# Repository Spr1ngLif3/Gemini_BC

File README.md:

<!-- PROJECT LOGO -->
<br />
<div align="center">

  <h3 align="center">Gemini Board Computer</h3>

  <p align="center">
    A simple and affordable board computer for bistage rockets!
    <br />
    <br />
    <a href="https://github.com/Spr1ngLif3/Gemini_BC/tree/master/software">Scripts</a>
    &middot;
    <a href="https://github.com/Spr1ngLif3/Gemini_BC/tree/master/hardware/gerbers">Gerbers</a>
    &middot;
    <a href="https://github.com/Spr1ngLif3/Gemini_BC/issues/new/choose">Request Feature</a>
  </p>
</div>

<!-- TABLE OF CONTENTS -->
<details>
  <summary>Table of Contents</summary>
  <ol>
    <li>
      <a href="#about-the-project">About The Project</a>
    </li>
    <li>
      <a href="#getting-started">Getting Started</a>
      <ul>
        <li><a href="#hardware">Hardware</a></li>
        <li><a href="#software">Software</a></li>
      </ul>
    </li>
    <li><a href="#usage">Usage</a></li>
    <li><a href="#contributing">Contributing</a></li>
    <li><a href="#license">License</a></li>
    <li><a href="#contact">Contact</a></li>
    <li><a href="#acknowledgments">Acknowledgments</a></li>
  </ol>
</details>

<!-- ABOUT THE PROJECT -->
## About The Project
<div align="center">

</div>

<br>

Building avionics for rockets can be really difficult: you have to choose the microcontroller, the sensors and how to use it for implement all the feature you want.

The experience looks overwhelming.

This is the right project for you! I developed a first simple platform to implement a complete bistage rocket avionic. This board contains the essential parts for satisfy only two tasks:

1. Starting the second stage of a rocket.
2. Log all the data from the launch in a microSD card.

I used a cheap and modular microcontroller (the Raspberry Pi Pico) for control all the components and I programmed it with the easiest programming language in the world: Python.

<p align="right">(<a href="#readme-top">back to top</a>)</p>

<!-- GETTING STARTED -->
## Getting Started

### Hardware

The board is designed with [KiCAD](https://kicad.org) software, an open source for making schematics and PCBs. 

For editing and take a look to the project, you can open KiCAD and select the option **Open Project (CTRL + O)** in the top-left menu.

After that, **select the .kicd_pro file** in the `hardware` folder.

If you want to send in production the board (with serivces like JLCPCB or PCBWay etc.) you can **zip the `gerbers` folder** and upload the zip file to the production service site. I can also modify the PCB and regenerate the gerbers via KiCAD and make your own board.

#### Note!!!
The KiCAD project needs the TP4056 battery manager footprint to work. You can find it in the `utils` folder. For help KiCAD recognize it, **move the .kicad_mod file in the same folder of the project file**. If you notice some problems, please open a issue or [contact me](#contact).

### Software

1. Install VSCode and setup the environment for the Raspberry Pi Pico. Check this [tutorial](https://randomnerdtutorials.com/raspberry-pi-pico-vs-code-micropython/) (not related to me).
2. Clone the repo.
   ```sh
   git clone https://github.com/Spr1ngLif3/Gemini_BC.git
   ```
3. Open the `software` folder in VSCode.
   ```sh
   code Gemini_BC/software
   ```
4. Now you can upload the basic script on the board with the command **MicroPico: Upload current file to Pico**. 

**Please do your checks before uploading the scripts and put the board inside a rocket! I'm not responsible for all missusage of this scripts.**

5. Board ready for launch.

<p align="right">(<a href="#readme-top">back to top</a>)</p>

<!-- USAGE EXAMPLES -->
## Usage

For using it in the wild (in the rocket), be careful to the polarity of the connectors on the board. The battery has a specific polarity but not the igniter (it should not care). I tested the board with some solid rocket engines designed for small rocket models, and I adjusted the timer for the second stage ignition based on the simulation and the specs of the engine.

The board can also charge the battery itself via USB-C with the TP4056 module on board.

Before the launch, be sure that the microSD card is correctly inserted and formatted in the FAT32 filesystem, the battery led is solid blue and the board is well secured on the rocket body.

After that, when you pull the switch to on the Pico boot and start executing the script loaded in it.

<p align="right">(<a href="#readme-top">back to top</a>)</p>

<!-- CONTRIBUTING -->
## Contributing

Contributions are what make the open source community such an amazing place to learn, inspire, and create. Any contributions you make are **greatly appreciated**.

If you have a suggestion that would make this better, please fork the repo and create a pull request. You can also simply open an issue.
Don't forget to give the project a star! Thanks again!

1. Fork the Project
2. Create your Feature Branch (`git checkout -b feature/AmazingFeature`)
3. Commit your Changes (`git commit -m 'Add some AmazingFeature'`)
4. Push to the Branch (`git push origin feature/AmazingFeature`)
5. Open a Pull Request

<p align="right">(<a href="#readme-top">back to top</a>)</p>

<!-- LICENSE -->
## License
Hardware files are licensed under CERN-OHL-S v2.

Software and scripts are licensed under GPLv3.

See `LICENSE` folder for more information.

<p align="right">(<a href="#readme-top">back to top</a>)</p>

<!-- CONTACT -->
## Contact

IG: [@ilvecchiourlatore](https://instagram.com/ilvecchiourlatore)

Website: [SpaceZero](https://spacezero.it)

<p align="right">(<a href="#readme-top">back to top</a>)</p>

<!-- ACKNOWLEDGMENTS -->
## Acknowledgments

I list here some resources that I feel useful for you:

* [MicroPython Docs](https://docs.micropython.org/en/latest/)
* [Raspberry Pi Pico Docs](https://www.raspberrypi.com/documentation/microcontrollers/pico-series.html)
* [KiCAD Docs](https://docs.kicad.org/)

<p align="right">(<a href="#readme-top">back to top</a>)</p>

Made with <3 by an hacker.

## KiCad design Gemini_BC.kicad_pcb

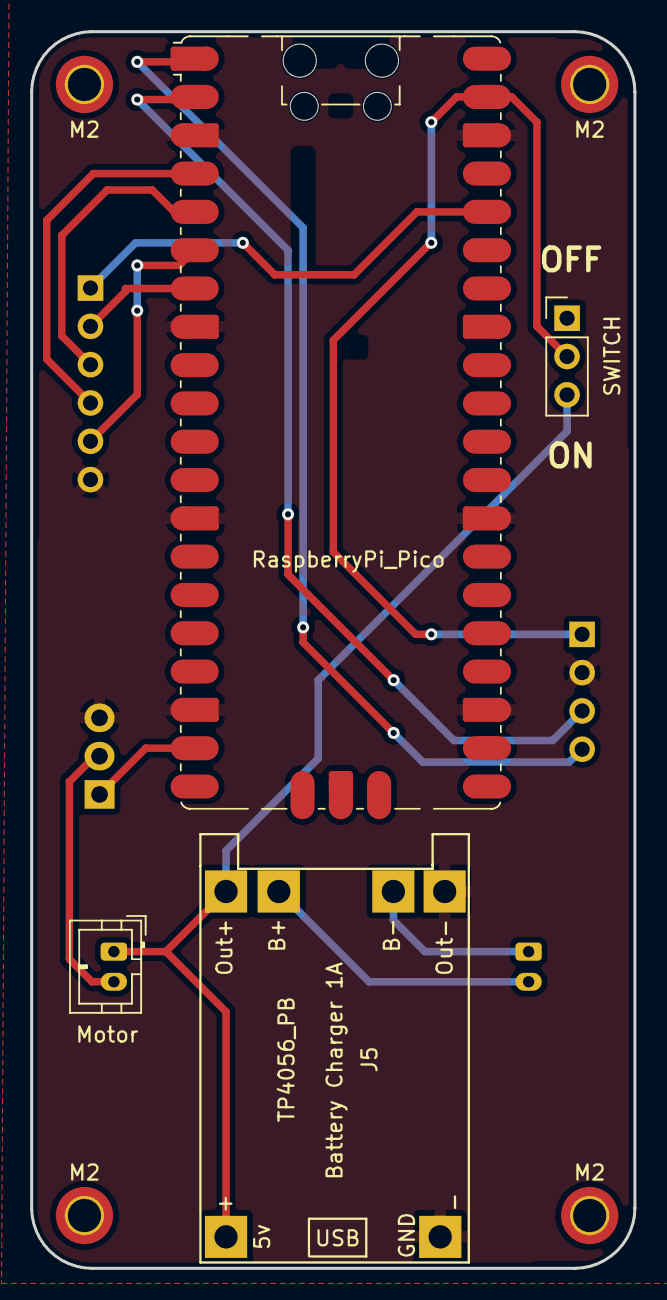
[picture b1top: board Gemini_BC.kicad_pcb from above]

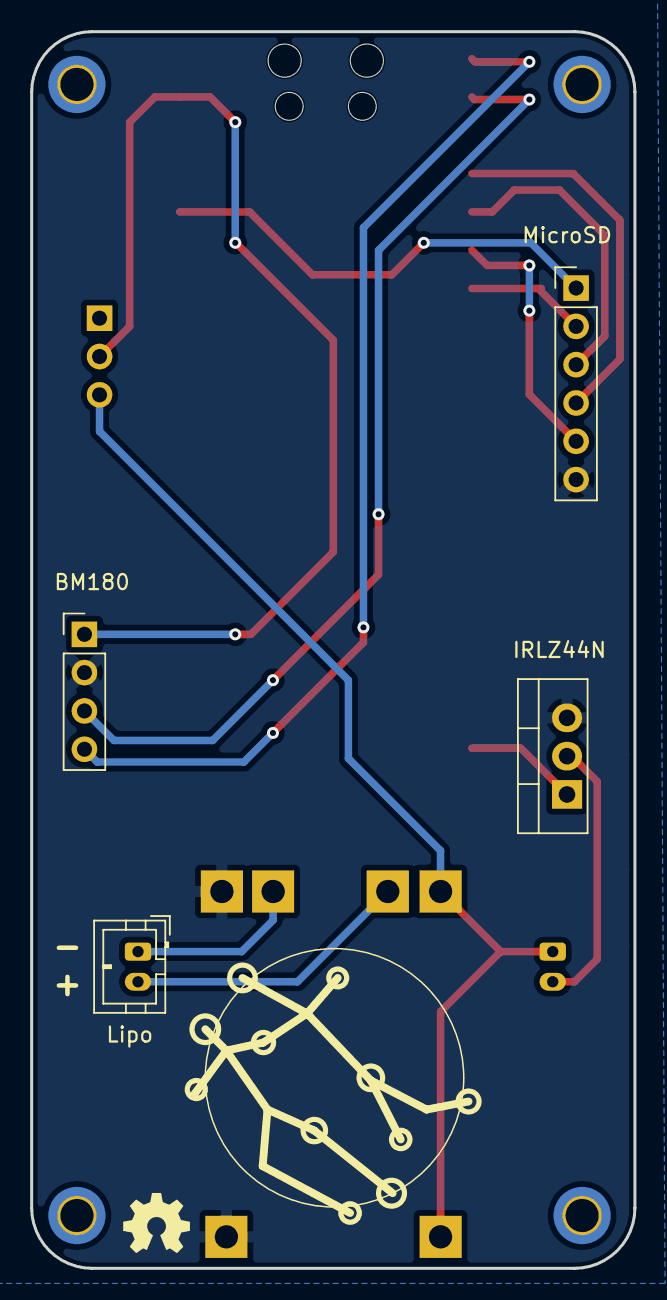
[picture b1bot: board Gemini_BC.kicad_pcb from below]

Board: 2 copper layers, 40.0 x 82.0 mm, 12 parts (4 on the bottom side), 14 nets.

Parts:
A1: RaspberryPi_Pico; RaspberryPi_Pico_SMD_HandSolder
J1: BM180; PinHeader_1x04_P2.54mm_Vertical
J2: MicroSD; PinHeader_1x06_P2.54mm_Vertical
J3: Lipo; JST_PH_B2B-PH-K_1x02_P2.00mm_Vertical
J4: Motor; JST_PH_B2B-PH-K_1x02_P2.00mm_Vertical
J5: TP4056_PB; TP4056-18650
M2, M2#2, M2#3, M2#4: MountingHole_2.2mm_M2_DIN965_Pad_TopBottom
Q1: IRLZ44N; TO-220-3_Vertical
SW1: SWITCH; PinHeader_1x03_P2.54mm_Vertical

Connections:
+3.3V: A1.36 (3V3), J2.1
+5V: A1.39 (VSYS), J1.1, J4.1 (-), SW1.2 (B)
+BATT: J3.2 (+), J5.5
-BATT: J3.1 (-), J5.6
BM180_SCL: A1.2 (GPIO1), J1.3
BM180_SDA: A1.1 (GPIO0), J1.4
GND: A1.3 (GND), A1.8 (GND), A1.13 (GND), A1.18 (GND), A1.23 (GND), A1.28 (GND), A1.38 (GND), A1.D2 (GND), J1.2, J2.6, J5.2, J5.4, Q1.3 (S)
MOTOR_CTRL: A1.19 (GPIO14), Q1.1 (G)
MOTOR_PIN: J4.2 (+), Q1.2 (D)
unnamed: J5.1, J5.3, SW1.3 (C)
SD_CLK: A1.4 (GPIO2), J2.4
SD_CS: A1.7 (GPIO5), J2.2
SD_MISO: A1.6 (GPIO4), J2.5
SD_MOSI: A1.5 (GPIO3), J2.3

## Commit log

2026-06-16 Init
2026-06-16 Added software, README and LICENSES
2026-06-16 Added git LFS
2026-06-16 README twicking
2026-06-16 More video twiks
2026-06-16 Mess with video solved
2026-06-16 REAL video solution
2026-06-16 Fixed README links
2026-06-16 README quick fix
